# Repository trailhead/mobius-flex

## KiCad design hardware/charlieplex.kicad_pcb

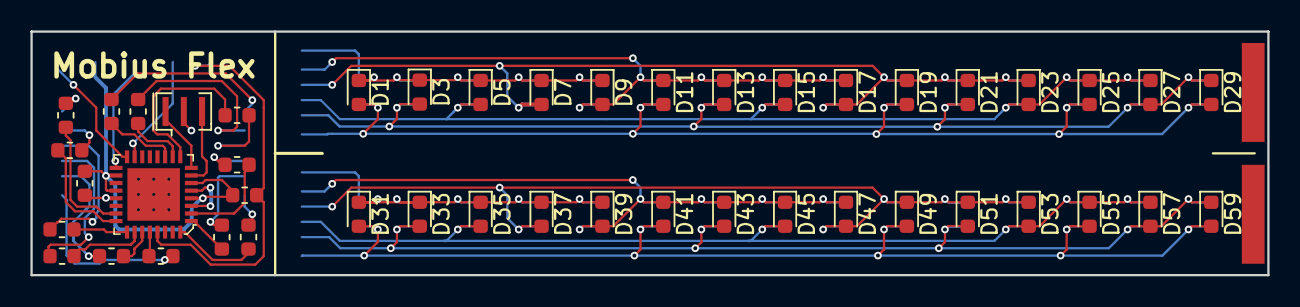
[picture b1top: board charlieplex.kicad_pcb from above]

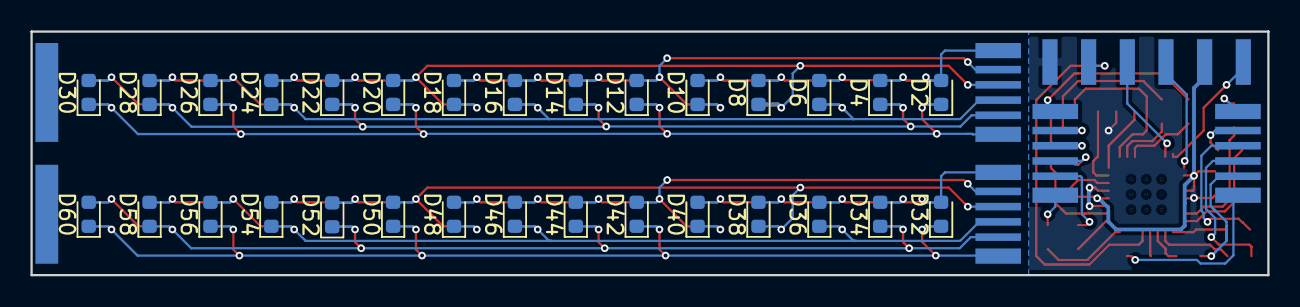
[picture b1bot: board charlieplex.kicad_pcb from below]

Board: 2 copper layers, 81.2 x 16.0 mm, 81 parts (35 on the bottom side), 44 nets.

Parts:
C1: C_Small; C_0603_1608Metric
D1, D2, D3, D4, D5, D6, D7, D8, D9, D10, D11, D12, D13, D14, D15, D16, D17, D18, D19, D20, D21, D22, D23, D24, D25, D26, D27, D28, D29, D30, D31, D32, D33, D34, D35, D36, D37, D38, D39, D40, D41, D42, D43, D44, D45, D46, D47, D48, D49, D50, D51, D52, D53, D54, D55, D56, D57, D58, D59, D60: R; LED_0603_1608Metric
J1: AVR-ISP-6; icsp_edge
J2, J3, J4, J5: pads; charlie_6pin
R1, R2, R3, R4, R5, R6, R7, R8, R9, R10, R11, R12, R13: R_Small; R_0603_1608Metric
U1: ATmega328P-AU; QFN-32-1EP_5x5mm
Y1: Resonator_Small; Resonator_SMD_muRata_CSTxExxV-3Pin_3.0x1.1mm

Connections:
+5V: C1.1, J1.2, R7.2, U1.4, U1.6, U1.18, U1.20
D1: R1.2, U1.11
D2: R2.2, U1.10
D3: R3.2, U1.9
D4: R4.2, U1.2
D5: R5.2, U1.1
D6: R6.2, U1.32
D7: R8.2, U1.23
D8: R9.2, U1.24
D9: R10.2, U1.25
D10: R11.2, U1.26
D11: R12.2, U1.27
D12: R13.2, U1.28
GND: C1.2, J1.6, U1.3, U1.5, U1.21, Y1.2
MISO: J1.1, U1.16
MOSI: J1.4, U1.15
unnamed: D1.1, D2.2, D3.1, D4.2, D5.1, D6.2, D7.1, D8.2, D9.1, D10.2, J3.1
unnamed: D1.2, D2.1, D11.2, D12.1, D19.2, D20.1, D25.2, D26.1, D29.2, D30.1, J3.6
unnamed: D9.2, D10.1, D11.1, D12.2, D13.1, D14.2, D15.1, D16.2, D17.1, D18.2, J3.2
unnamed: D3.2, D4.1, D13.2, D14.1, D21.2, D22.1, D27.2, D28.1, D29.1, D30.2, J3.5
unnamed: D5.2, D6.1, D15.2, D16.1, D23.2, D24.1, D25.1, D26.2, D27.1, D28.2, J3.4
unnamed: D7.2, D8.1, D17.2, D18.1, D19.1, D20.2, D21.1, D22.2, D23.1, D24.2, J3.3
unnamed: D31.1, D32.2, D33.1, D34.2, D35.1, D36.2, D37.1, D38.2, D39.1, D40.2, J5.1
unnamed: D31.2, D32.1, D41.2, D42.1, D49.2, D50.1, D55.2, D56.1, D59.2, D60.1, J5.6
unnamed: D33.2, D34.1, D43.2, D44.1, D51.2, D52.1, D57.2, D58.1, D59.1, D60.2, J5.5
unnamed: D35.2, D36.1, D45.2, D46.1, D53.2, D54.1, D55.1, D56.2, D57.1, D58.2, J5.4
unnamed: D37.2, D38.1, D47.2, D48.1, D49.1, D50.2, D51.1, D52.2, D53.1, D54.2, J5.3
unnamed: D39.2, D40.1, D41.1, D42.2, D43.1, D44.2, D45.1, D46.2, D47.1, D48.2, J5.2
unnamed: J2.1, R1.1
unnamed: J2.2, R2.1
unnamed: J2.3, R3.1
unnamed: J2.4, R4.1
unnamed: J2.5, R5.1
unnamed: J2.6, R6.1
unnamed: J4.1, R8.1
unnamed: J4.2, R9.1
unnamed: J4.3, R10.1
unnamed: J4.4, R11.1
unnamed: J4.5, R12.1
unnamed: J4.6, R13.1
unnamed: U1.7, Y1.3
unnamed: U1.8, Y1.1
RESET: J1.5, R7.1, U1.29
SCK: J1.3, U1.17

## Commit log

2019-04-09 adding firmware
